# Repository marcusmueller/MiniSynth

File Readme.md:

# MiniSynth

A small, MAX2870-based synthesizer with integrated oscillator or selectable
external reference clock input.

Done in KiCad.

Central components:

* Maxim MAX2870: Fractional-N Synthesizer
* Anaren B0430J50100AHF: Wideband Balun to convert MAX2870's differential output(s) to single-ended
* FOX924B: 16 MHz Oscillator
* The tears of a million coffee beans

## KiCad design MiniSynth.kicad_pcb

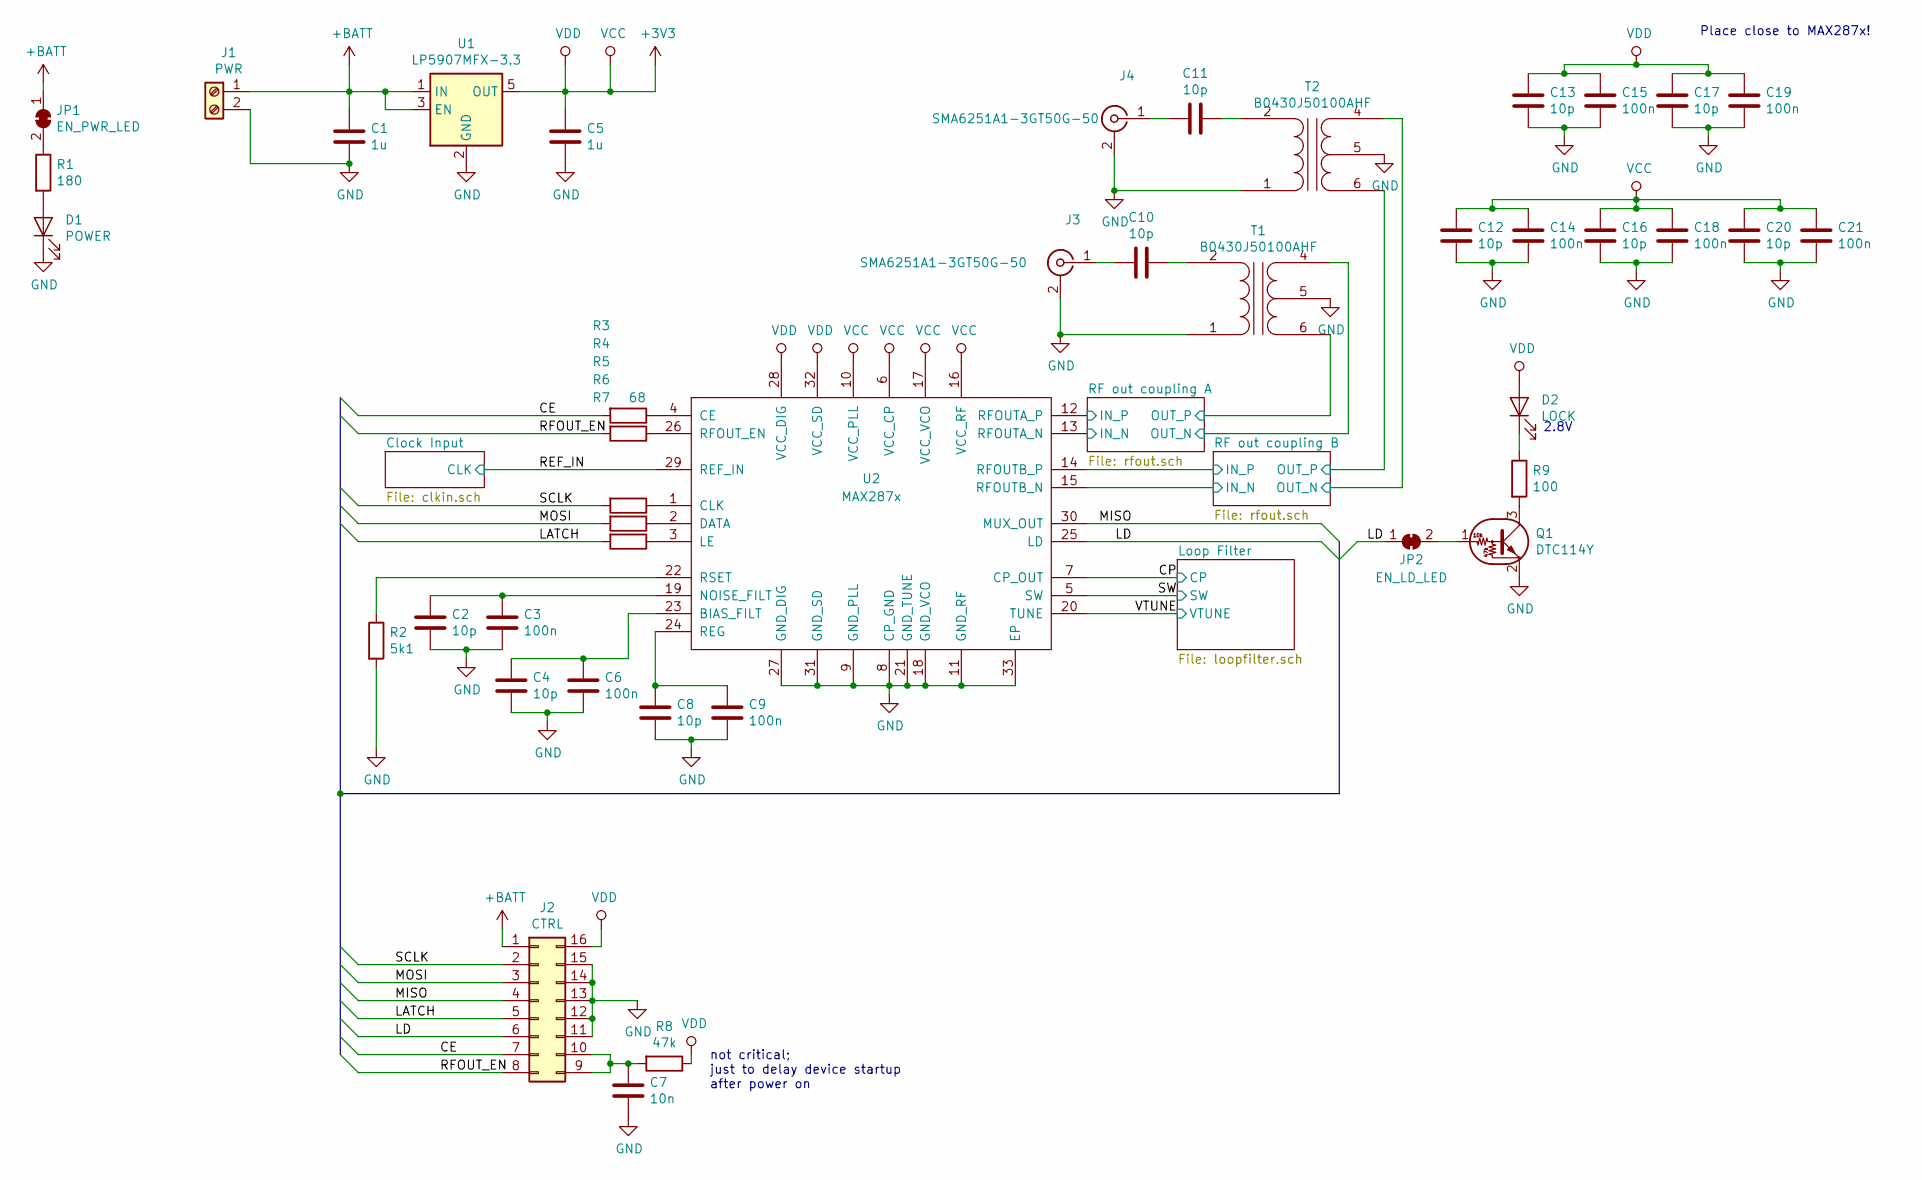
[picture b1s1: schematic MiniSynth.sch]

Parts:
C1, C5: 1u; C_0603_1608Metric
C2, C4, C8, C12, C13, C16, C17, C20: 10p; C_0603_1608Metric
C3, C6, C9, C14, C15, C18, C19, C21: 100n; C_0603_1608Metric
C7: 10n; C_0603_1608Metric
C10, C11: 10p; C_0402_1005Metric
D1: POWER; LED_0805_2012Metric_Castellated
D2: LOCK; LED_0805_2012Metric_Castellated
J1: PWR; TerminalBlock_Altech_AK300-2_P5.00mm
J2: CTRL; Multicomp_MC9A12-1634_2x08_P2.54mm_Vertical
J3, J4: SMA6251A1-3GT50G-50; SMA_Amphenol_132134-16_Vertical
JP1: EN_PWR_LED; SolderJumper-2_P1.3mm_Open_TrianglePad1.0x1.5mm
JP2: EN_LD_LED; SolderJumper-2_P1.3mm_Open_TrianglePad1.0x1.5mm
Q1: DTC114Y; SOT-416
R1: 180; R_0603_1608Metric
R2: 5k1; R_0603_1608Metric
R3, R4, R5, R6, R7: 68; R_0603_1608Metric
R8: 47k; R_0603_1608Metric
R9: 100; R_0603_1608Metric
T1, T2: B0430J50100AHF
U1: LP5907MFX-3.3; SOT-23-5
U2: MAX287x; QFN-32-1EP_5x5mm_P0.5mm_EP3.1x3.1mm_ThermalVias

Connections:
+3V3: C5.1, C12.2, C13.2, C14.2, C15.2, C16.2, C17.2, C18.2, C19.2, C20.2, C21.2, D2.2 (A), J2.16, R8.1, U1.5 (OUT), U2.6 (VCC_CP), U2.10 (VCC_PLL), U2.16 (VCC_RF), U2.17 (VCC_VCO), U2.28 (VCC_DIG), U2.32 (VCC_SD); also elsewhere on the board
+BATT: C1.1, J1.1, J2.1, JP1.1 (A), U1.1 (IN), U1.3 (EN)
/CE: J2.7, R3.2
/CP: U2.7 (CP_OUT); also elsewhere on the board
/LATCH: J2.5, R7.2
/LD: J2.6, JP2.1 (A), U2.25 (LD)
/MISO: J2.4, U2.30 (MUX_OUT)
/MOSI: J2.3, R6.2
/REF_IN: U2.29 (REF_IN); also elsewhere on the board
/RF out coupling A/IN_N: U2.13 (RFOUTA_N); also elsewhere on the board
/RF out coupling A/IN_P: U2.12 (RFOUTA_P); also elsewhere on the board
/RF out coupling A/OUT_N: T1.4 (BAL1); also elsewhere on the board
/RF out coupling A/OUT_P: T1.6 (BAL2); also elsewhere on the board
/RF out coupling B/IN_N: U2.15 (RFOUTB_N); also elsewhere on the board
/RF out coupling B/IN_P: U2.14 (RFOUTB_P); also elsewhere on the board
/RF out coupling B/OUT_N: T2.4 (BAL1); also elsewhere on the board
/RF out coupling B/OUT_P: T2.6 (BAL2); also elsewhere on the board
/RFOUT_EN: J2.8, R4.2
/SCLK: J2.2, R5.2
/SW: U2.5 (SW); also elsewhere on the board
/VTUNE: U2.20 (TUNE); also elsewhere on the board
GND: C1.2, C2.1, C3.1, C4.1, C5.2, C6.1, C7.2, C8.1, C9.1, C12.1, C13.1, C14.1, C15.1, C16.1, C17.1, C18.1, C19.1, C20.1, C21.1, D1.1 (K), J1.2, J2.11, J2.12, J2.13, J2.14, J2.15, J3.2 (Ext), J4.2 (Ext), Q1.2 (E), R2.2, T1.1 (GND), T1.3 (GND), T1.5, T2.1 (GND), T2.3 (GND), T2.5, U1.2 (GND), U2.8 (CP_GND), U2.9 (GND_PLL), U2.11 (GND_RF), U2.18 (GND_VCO), U2.21 (GND_TUNE), U2.27 (GND_DIG), U2.31 (GND_SD), U2.33 (EP); also elsewhere on the board
unnamed: C2.2, C3.2, U2.19 (NOISE_FILT)
unnamed: C4.2, C6.2, U2.23 (BIAS_FILT)
unnamed: C7.1, J2.9, J2.10, R8.2
unnamed: C8.2, C9.2, U2.24 (REG)
unnamed: C10.1, T1.2 (UNB)
unnamed: C10.2, J3.1 (In)
unnamed: C11.1, T2.2 (UNB)
unnamed: C11.2, J4.1 (In)
unnamed: D1.2 (A), R1.2
unnamed: D2.1 (K), R9.1
unnamed: JP1.2 (B), R1.1
unnamed: JP2.2 (B), Q1.1 (B)
unnamed: Q1.3 (C), R9.2
unnamed: R2.1, U2.22 (RSET)
unnamed: R3.1, U2.4 (CE)
unnamed: R4.1, U2.26 (RFOUT_EN)
unnamed: R5.1, U2.1 (CLK)
unnamed: R6.1, U2.2 (DATA)
unnamed: R7.1, U2.3 (LE)

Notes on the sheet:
2.8V
not critical; just to delay device startup after power on
Place close to MAX287x!

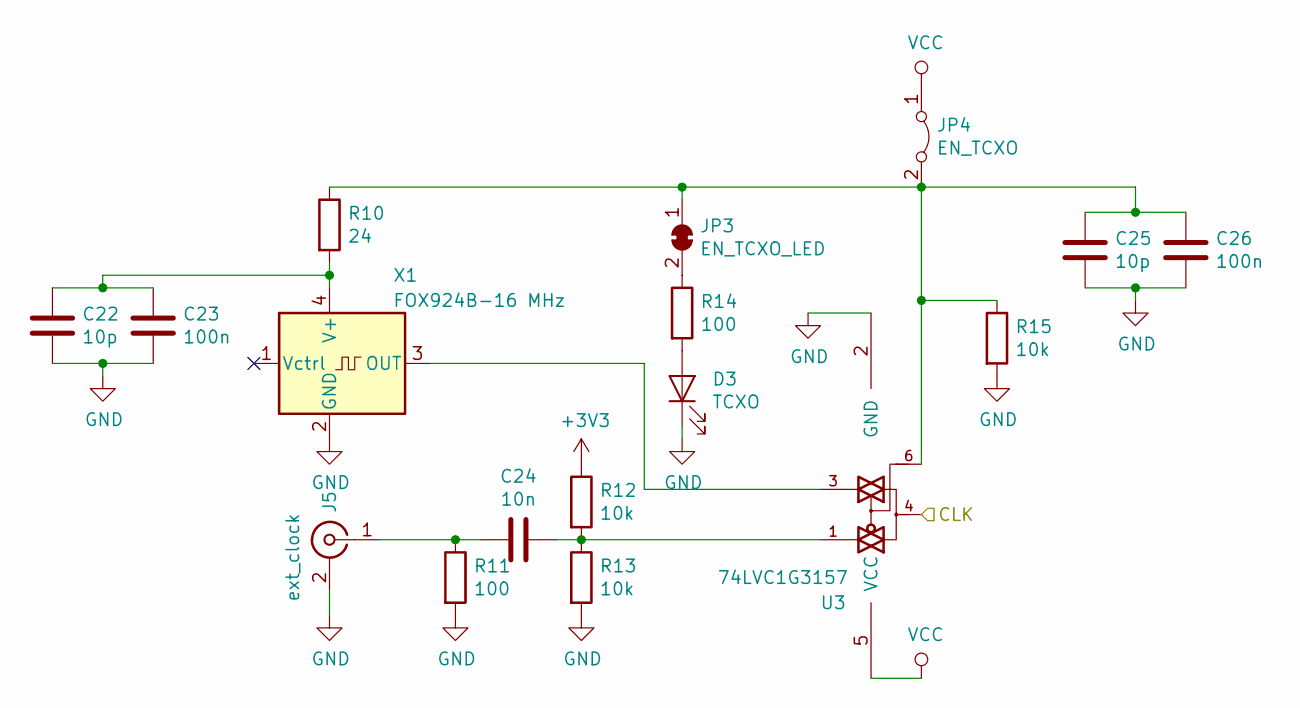
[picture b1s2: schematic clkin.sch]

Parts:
C22, C25: 10p; C_0603_1608Metric
C23, C26: 100n; C_0603_1608Metric
C24: 10n; C_0603_1608Metric
D3: TCXO; LED_0805_2012Metric_Castellated
J5: ext_clock; SMA_Amphenol_132134-16_Vertical
JP3: EN_TCXO_LED; SolderJumper-2_P1.3mm_Open_TrianglePad1.0x1.5mm
JP4: EN_TCXO; PinHeader_1x02_P2.54mm_Vertical
R10: 24; R_0603_1608Metric
R11, R14: 100; R_0603_1608Metric
R12, R13, R15: 10k; R_0603_1608Metric
U3: 74LVC1G3157; SOT-23-6
X1: FOX924B-16 MHz; Oscillator_SMD_Fordahl_DFAS15-4Pin_5.0x3.2mm

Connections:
+3V3: JP4.1 (A), R12.1, U3.5 (VCC); also elsewhere on the board
/REF_IN: U3.4; also elsewhere on the board
GND: C22.1, C23.1, C25.1, C26.1, D3.1 (K), J5.2 (Ext), R11.2, R13.2, R15.2, U3.2 (GND), X1.2 (GND); also elsewhere on the board
unnamed: C22.2, C23.2, R10.2, X1.4 (V+)
unnamed: C24.1, R12.2, R13.1, U3.1
unnamed: C24.2, J5.1 (In), R11.1
unnamed: C25.2, C26.2, JP3.1 (A), JP4.2 (B), R10.1, R15.1, U3.6
unnamed: D3.2 (A), R14.2
unnamed: JP3.2 (B), R14.1
unnamed: U3.3, X1.3 (OUT)

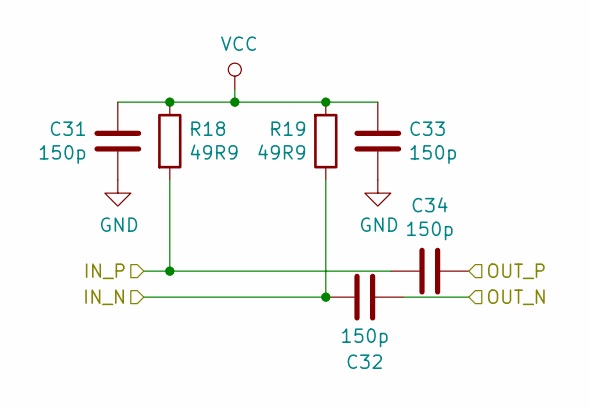
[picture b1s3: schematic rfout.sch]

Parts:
C27, C28, C29, C30: 150p; C_0402_1005Metric
R16, R17: 49R9; R_0402_1005Metric

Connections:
+3V3: C27.2, C29.1, R16.1, R17.2; also elsewhere on the board
/RF out coupling A/IN_N: C28.1, R17.1; also elsewhere on the board
/RF out coupling A/IN_P: C30.1, R16.2; also elsewhere on the board
/RF out coupling A/OUT_N: C28.2; also elsewhere on the board
/RF out coupling A/OUT_P: C30.2; also elsewhere on the board
GND: C27.1, C29.2; also elsewhere on the board

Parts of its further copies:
C31, C32, C33, C34: 150p; C_0402_1005Metric
R18, R19: 49R9; R_0402_1005Metric

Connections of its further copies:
+3V3: C31.2, C33.1, R18.1, R19.2; also elsewhere on the board
/RF out coupling B/IN_N: C32.1, R19.1; also elsewhere on the board
/RF out coupling B/IN_P: C34.1, R18.2; also elsewhere on the board
/RF out coupling B/OUT_N: C32.2; also elsewhere on the board
/RF out coupling B/OUT_P: C34.2; also elsewhere on the board
GND: C31.1, C33.2; also elsewhere on the board

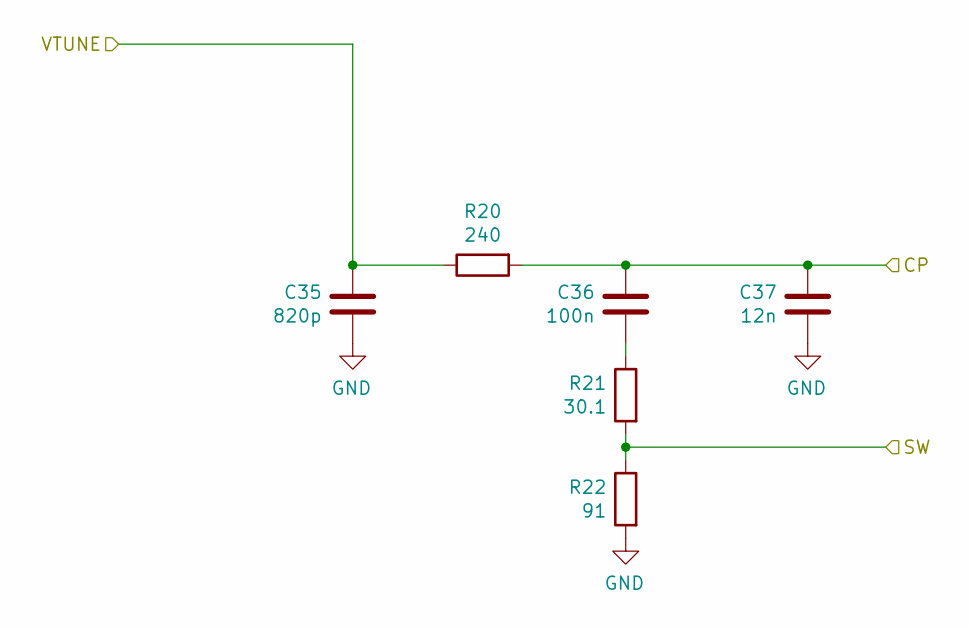
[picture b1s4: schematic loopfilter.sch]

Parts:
C35: 820p; C_0603_1608Metric
C36: 100n; C_0603_1608Metric
C37: 12n; C_0603_1608Metric
R20: 240; R_0603_1608Metric
R21: 30.1; R_0603_1608Metric
R22: 91; R_0603_1608Metric

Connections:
/CP: C36.1, C37.1, R20.2; also elsewhere on the board
/SW: R21.2, R22.1; also elsewhere on the board
/VTUNE: C35.1, R20.1; also elsewhere on the board
GND: C35.2, C37.2, R22.2; also elsewhere on the board
unnamed: C36.2, R21.1

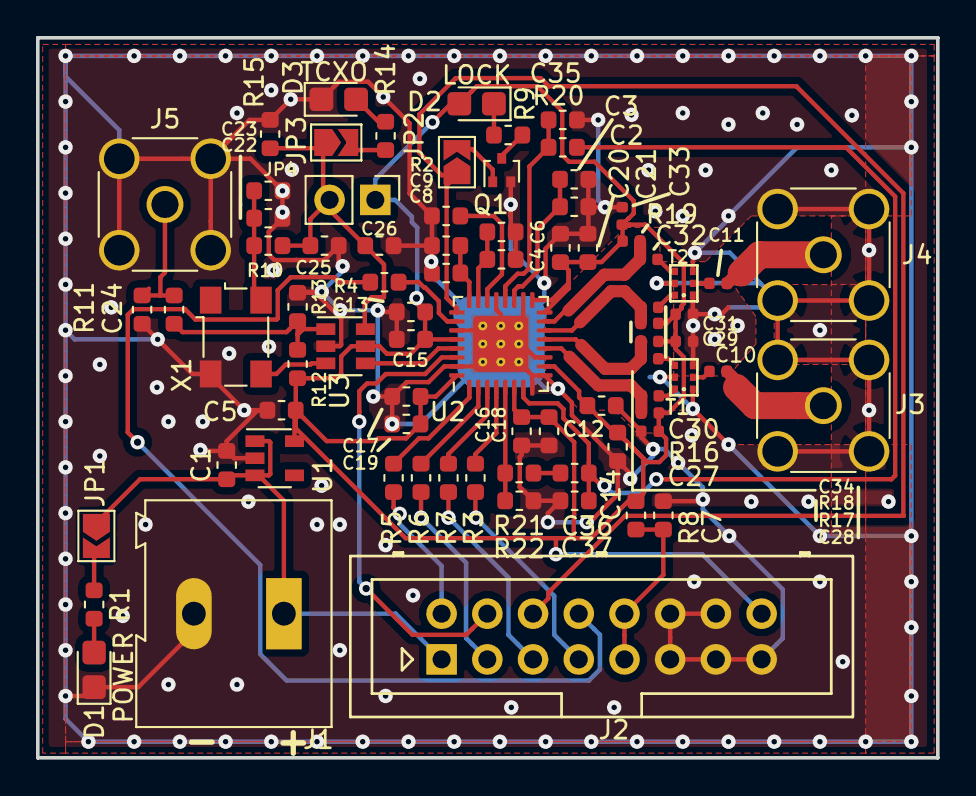
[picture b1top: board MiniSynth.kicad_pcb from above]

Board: 2 copper layers, 50.0 x 40.0 mm, 78 parts (0 on the bottom side), 49 nets.

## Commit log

2019-03-03 added analog switch symbol with explicit power pins (ugly)
2019-03-03 Readme and Rendering
2019-03-03 Balun Footprint
2019-03-03 initial
